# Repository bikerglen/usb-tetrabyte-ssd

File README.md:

# usb-tetrabyte-ssd

inspired by https://twitter.com/NanoRaptor/status/1473796625403301888

Hardware design files and software posted!

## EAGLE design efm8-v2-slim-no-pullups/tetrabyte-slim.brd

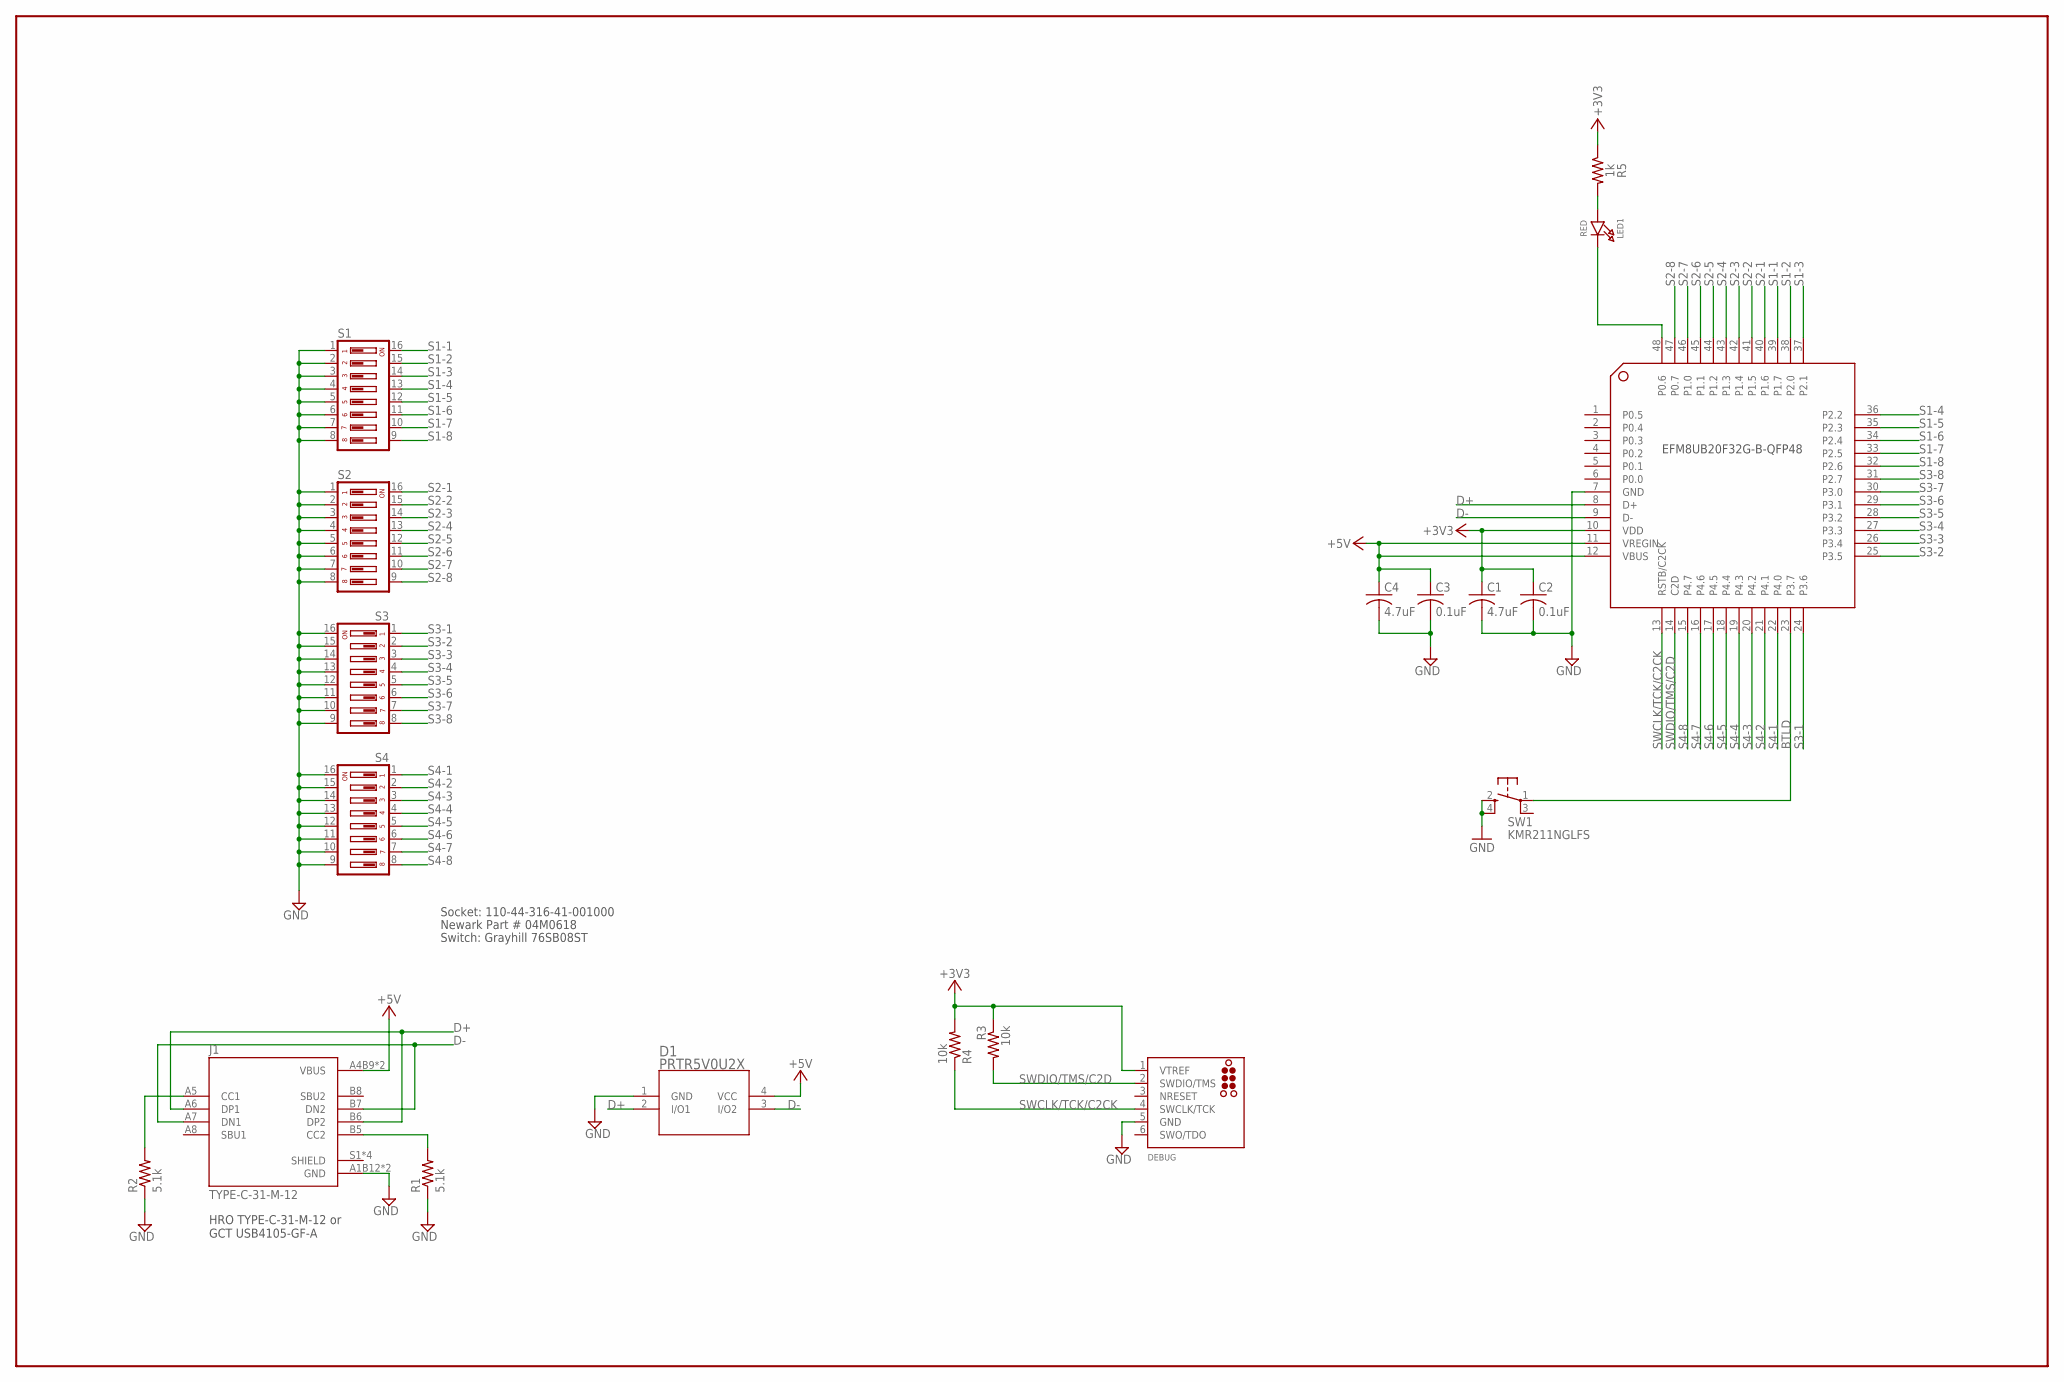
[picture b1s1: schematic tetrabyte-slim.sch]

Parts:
C1, C4: 4.7uF; C0603K
C2, C3: 0.1uF; C0603K
D1: PRTR5V0U2X; SOT143B
DEBUG: TC2030-CTX-SWD; TC2030-MCP-NL
J1: TYPE-C-31-M-12; HRO_TYPE-C-31-M-12
LED1: RED; CHIPLED_0805_NOOUTLINE
R1, R2: 5.1k; R0603
R3, R4: 10k; R0603
R5: 1k; R0603
S1, S2, S3, S4: DS08; DS-08
SW1: KMR211NGLFS; KMR2
U1: EFM8UB20F64G-B-QFP48; EFM8UB2-QFP48

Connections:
+3V3: C1.1, C2.1, DEBUG.1 (VTREF), R3.1, R4.2, R5.1, U1.10 (VDD)
+5V: C3.1, C4.1, D1.4 (VCC), J1.A4B9 (VBUS), J1.B4A9 (VBUS), U1.11 (VREGIN), U1.12 (VBUS)
BTLD: SW1.1, U1.23 (P3.7)
D+: D1.2 (I/O1), J1.A6 (DP1), J1.B6 (DP2), U1.8 (D+)
D-: D1.3 (I/O2), J1.A7 (DN1), J1.B7 (DN2), U1.9 (D-)
GND: C1.2, C2.2, C3.2, C4.2, D1.1 (GND), DEBUG.5 (GND), J1.A1B12 (GND), J1.B1A12 (GND), R1.1, R2.1, S1.1, S1.2, S1.3, S1.4, S1.5, S1.6, S1.7, S1.8, S2.1, S2.2, S2.3, S2.4, S2.5, S2.6, S2.7, S2.8, S3.9, S3.10, S3.11, S3.12, S3.13, S3.14, S3.15, S3.16, S4.9, S4.10, S4.11, S4.12, S4.13, S4.14, S4.15, S4.16, SW1.2 (S), SW1.4 (S1), U1.7 (GND)
unnamed: LED1.A, R5.2
unnamed: LED1.C, U1.48 (P0.6)
unnamed: J1.B5 (CC2), R1.2
unnamed: J1.A5 (CC1), R2.2
NRESET: DEBUG.3 (NRESET)
S1-1: S1.16, U1.39 (P1.7)
S1-2: S1.15, U1.38 (P2.0)
S1-3: S1.14, U1.37 (P2.1)
S1-4: S1.13, U1.36 (P2.2)
S1-5: S1.12, U1.35 (P2.3)
S1-6: S1.11, U1.34 (P2.4)
S1-7: S1.10, U1.33 (P2.5)
S1-8: S1.9, U1.32 (P2.6)
S2-1: S2.16, U1.40 (P1.6)
S2-2: S2.15, U1.41 (P1.5)
S2-3: S2.14, U1.42 (P1.4)
S2-4: S2.13, U1.43 (P1.3)
S2-5: S2.12, U1.44 (P1.2)
S2-6: S2.11, U1.45 (P1.1)
S2-7: S2.10, U1.46 (P1.0)
S2-8: S2.9, U1.47 (P0.7)
S3-1: S3.1, U1.24 (P3.6)
S3-2: S3.2, U1.25 (P3.5)
S3-3: S3.3, U1.26 (P3.4)
S3-4: S3.4, U1.27 (P3.3)
S3-5: S3.5, U1.28 (P3.2)
S3-6: S3.6, U1.29 (P3.1)
S3-7: S3.7, U1.30 (P3.0)
S3-8: S3.8, U1.31 (P2.7)
S4-1: S4.1, U1.22 (P4.0)
S4-2: S4.2, U1.21 (P4.1)
S4-3: S4.3, U1.20 (P4.2)
S4-4: S4.4, U1.19 (P4.3)
S4-5: S4.5, U1.18 (P4.4)
S4-6: S4.6, U1.17 (P4.5)
S4-7: S4.7, U1.16 (P4.6)
S4-8: S4.8, U1.15 (P4.7)
SWCLK/TCK/C2CK: DEBUG.4 (SWCLK/TCK), R4.1, U1.13 (RSTB/C2CK)
SWDIO/TMS/C2D: DEBUG.2 (SWDIO/TMS), R3.2, U1.14 (C2D)

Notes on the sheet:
EFM8UB20F32G-B-QFP48
Socket: 110-44-316-41-001000
Newark Part # 04M0618
Switch: Grayhill 76SB08ST
HRO TYPE-C-31-M-12 or GCT USB4105-GF-A

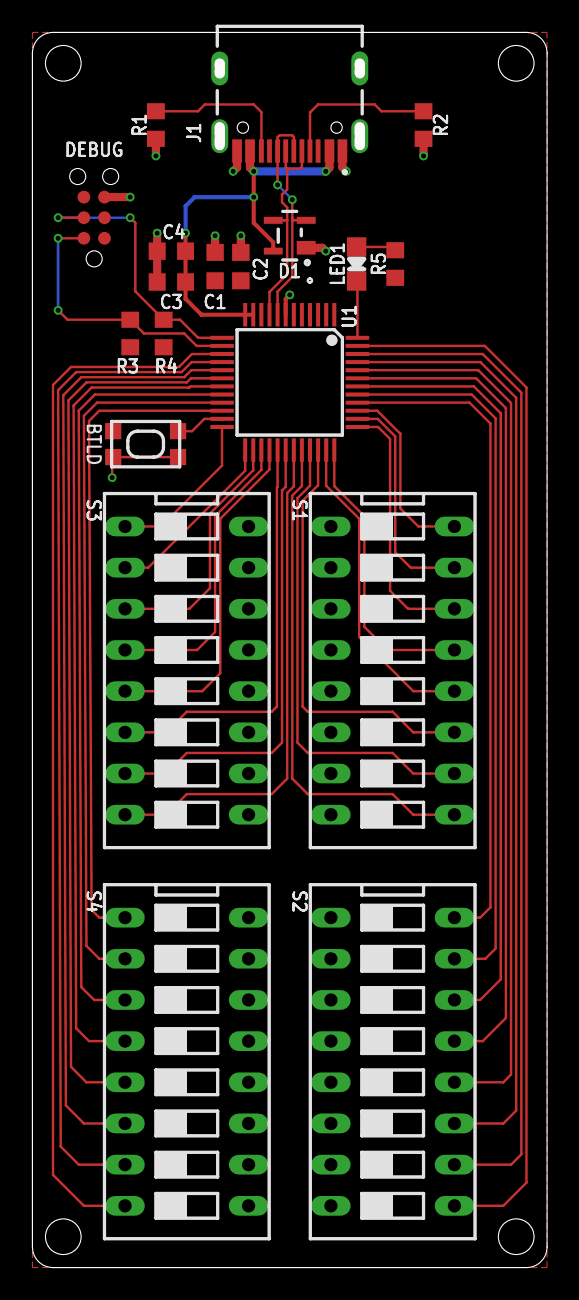
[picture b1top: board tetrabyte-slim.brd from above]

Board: 2 copper layers, 31.1 x 75.5 mm, 19 parts (0 on the bottom side), 44 nets.

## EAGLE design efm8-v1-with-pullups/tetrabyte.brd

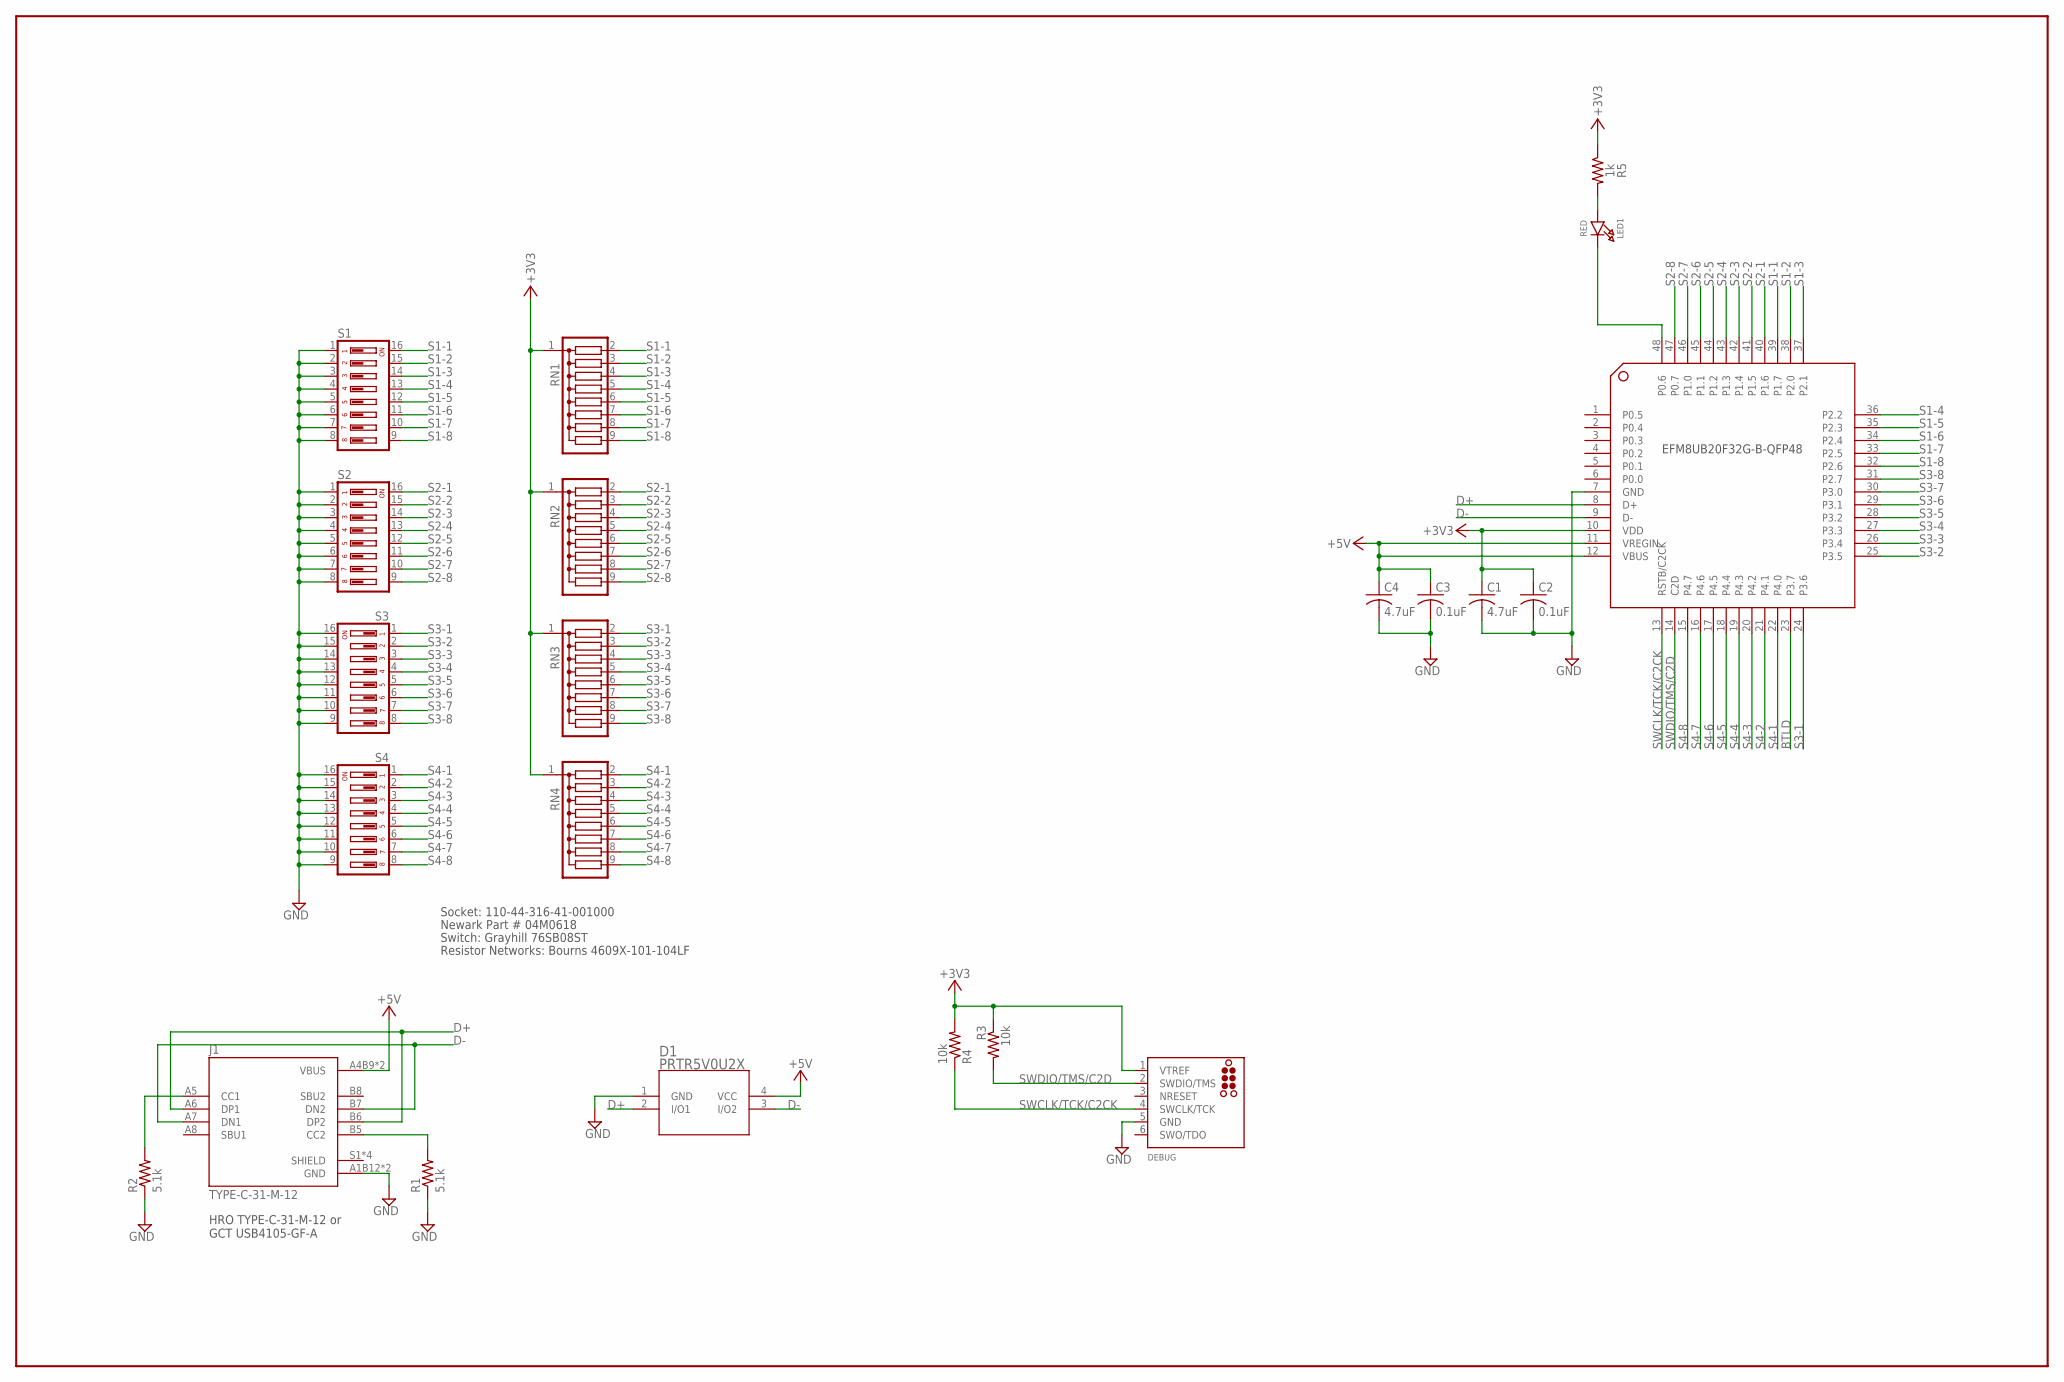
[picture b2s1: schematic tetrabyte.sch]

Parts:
C1, C4: 4.7uF; C0603K
C2, C3: 0.1uF; C0603K
D1: PRTR5V0U2X; SOT143B
DEBUG: TC2030-CTX-SWD; TC2030-MCP-NL
J1: TYPE-C-31-M-12; HRO_TYPE-C-31-M-12
LED1: RED; CHIPLED_0805_NOOUTLINE
R1, R2: 5.1k; R0603
R3, R4: 10k; R0603
R5: 1k; R0603
RN1, RN2, RN3, RN4: G08R; SIL9
S1, S2, S3, S4: DS08; DS-08
U1: EFM8UB20F64G-B-QFP48; EFM8UB2-QFP48

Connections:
+3V3: C1.1, C2.1, DEBUG.1 (VTREF), R3.1, R4.2, R5.1, RN1.1, RN2.1, RN3.1, RN4.1, U1.10 (VDD)
+5V: C3.1, C4.1, D1.4 (VCC), J1.A4B9 (VBUS), J1.B4A9 (VBUS), U1.11 (VREGIN), U1.12 (VBUS)
BTLD: U1.23 (P3.7)
D+: D1.2 (I/O1), J1.A6 (DP1), J1.B6 (DP2), U1.8 (D+)
D-: D1.3 (I/O2), J1.A7 (DN1), J1.B7 (DN2), U1.9 (D-)
GND: C1.2, C2.2, C3.2, C4.2, D1.1 (GND), DEBUG.5 (GND), J1.A1B12 (GND), J1.B1A12 (GND), R1.1, R2.1, S1.1, S1.2, S1.3, S1.4, S1.5, S1.6, S1.7, S1.8, S2.1, S2.2, S2.3, S2.4, S2.5, S2.6, S2.7, S2.8, S3.9, S3.10, S3.11, S3.12, S3.13, S3.14, S3.15, S3.16, S4.9, S4.10, S4.11, S4.12, S4.13, S4.14, S4.15, S4.16, U1.7 (GND)
unnamed: LED1.A, R5.2
unnamed: LED1.C, U1.48 (P0.6)
unnamed: J1.B5 (CC2), R1.2
unnamed: J1.A5 (CC1), R2.2
NRESET: DEBUG.3 (NRESET)
S1-1: RN1.2, S1.16, U1.39 (P1.7)
S1-2: RN1.3, S1.15, U1.38 (P2.0)
S1-3: RN1.4, S1.14, U1.37 (P2.1)
S1-4: RN1.5, S1.13, U1.36 (P2.2)
S1-5: RN1.6, S1.12, U1.35 (P2.3)
S1-6: RN1.7, S1.11, U1.34 (P2.4)
S1-7: RN1.8, S1.10, U1.33 (P2.5)
S1-8: RN1.9, S1.9, U1.32 (P2.6)
S2-1: RN2.2, S2.16, U1.40 (P1.6)
S2-2: RN2.3, S2.15, U1.41 (P1.5)
S2-3: RN2.4, S2.14, U1.42 (P1.4)
S2-4: RN2.5, S2.13, U1.43 (P1.3)
S2-5: RN2.6, S2.12, U1.44 (P1.2)
S2-6: RN2.7, S2.11, U1.45 (P1.1)
S2-7: RN2.8, S2.10, U1.46 (P1.0)
S2-8: RN2.9, S2.9, U1.47 (P0.7)
S3-1: RN3.2, S3.1, U1.24 (P3.6)
S3-2: RN3.3, S3.2, U1.25 (P3.5)
S3-3: RN3.4, S3.3, U1.26 (P3.4)
S3-4: RN3.5, S3.4, U1.27 (P3.3)
S3-5: RN3.6, S3.5, U1.28 (P3.2)
S3-6: RN3.7, S3.6, U1.29 (P3.1)
S3-7: RN3.8, S3.7, U1.30 (P3.0)
S3-8: RN3.9, S3.8, U1.31 (P2.7)
S4-1: RN4.2, S4.1, U1.22 (P4.0)
S4-2: RN4.3, S4.2, U1.21 (P4.1)
S4-3: RN4.4, S4.3, U1.20 (P4.2)
S4-4: RN4.5, S4.4, U1.19 (P4.3)
S4-5: RN4.6, S4.5, U1.18 (P4.4)
S4-6: RN4.7, S4.6, U1.17 (P4.5)
S4-7: RN4.8, S4.7, U1.16 (P4.6)
S4-8: RN4.9, S4.8, U1.15 (P4.7)
SWCLK/TCK/C2CK: DEBUG.4 (SWCLK/TCK), R4.1, U1.13 (RSTB/C2CK)
SWDIO/TMS/C2D: DEBUG.2 (SWDIO/TMS), R3.2, U1.14 (C2D)

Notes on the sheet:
EFM8UB20F32G-B-QFP48
Socket: 110-44-316-41-001000
Newark Part # 04M0618
Switch: Grayhill 76SB08ST
Resistor Networks: Bourns 4609X-101-104LF
HRO TYPE-C-31-M-12 or GCT USB4105-GF-A

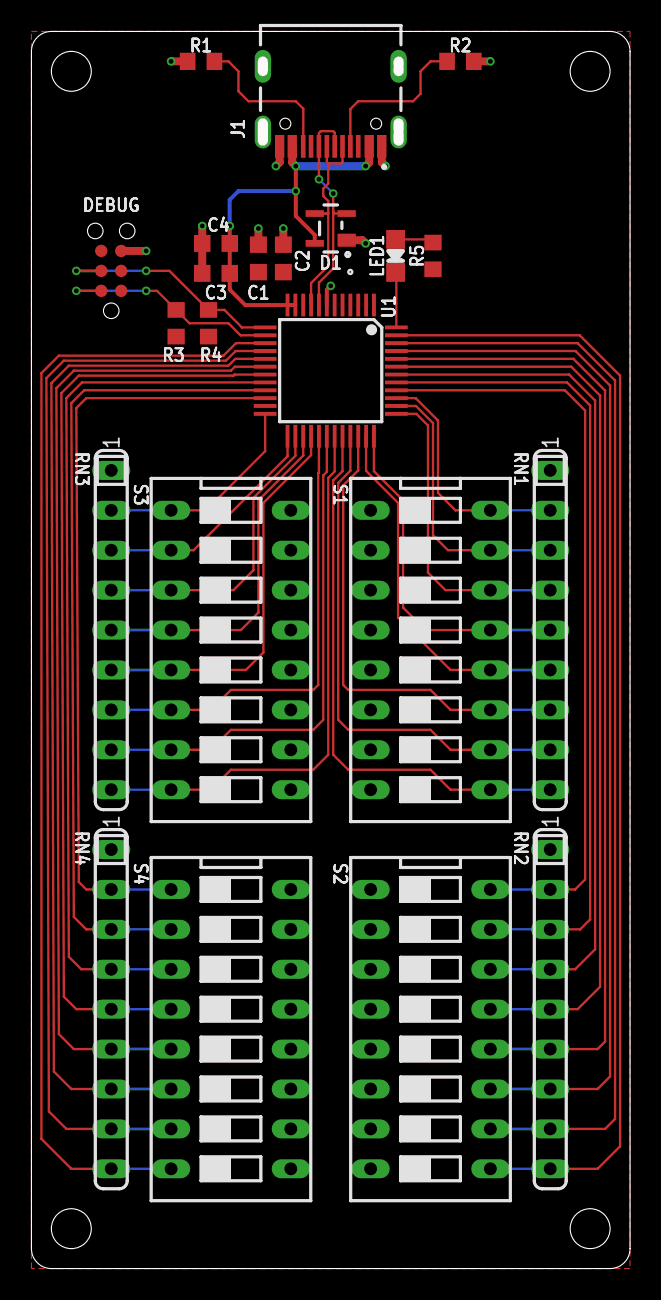
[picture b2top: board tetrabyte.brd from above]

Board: 2 copper layers, 37.4 x 78.1 mm, 22 parts (0 on the bottom side), 43 nets.

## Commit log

2022-01-20 initial checkin of board design files
2022-01-20 added software to library
2022-01-23 add bootload switch

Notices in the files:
parts and their libraries:
tag-connect: ©2009 ROFA.cz - modified and updated by Robert Darlington ‹rdarlington@gmail.com›
microbuilder: This work is placed in the public domain, and may be freely used for commercial and non-commercial work with the following conditions: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
